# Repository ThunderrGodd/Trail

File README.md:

A copy of Promenade keyboard PCB, based on ChillKB's ice60v2.
<br />It's still WIP, but I don't want to manage it anymore.
<br />Working NEVER tested

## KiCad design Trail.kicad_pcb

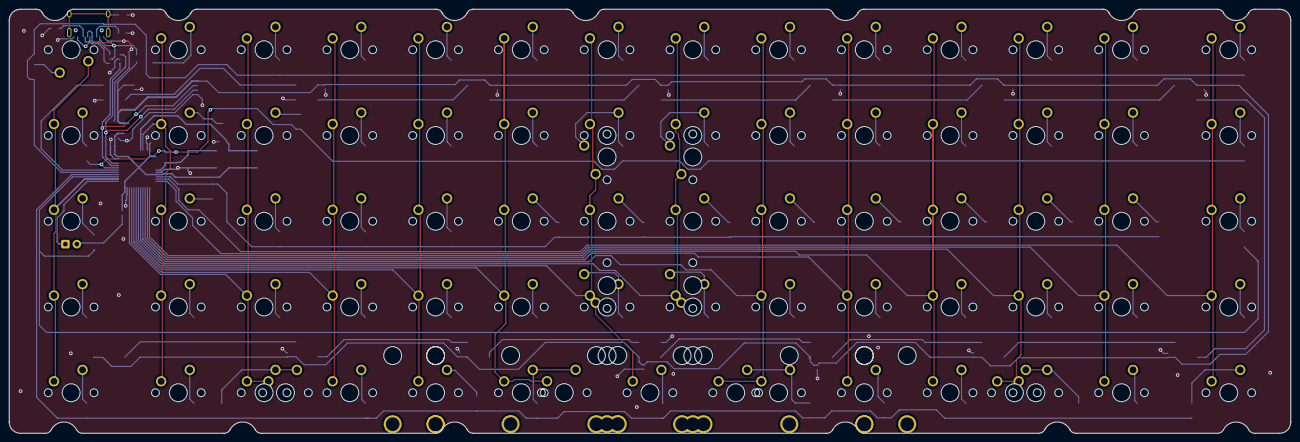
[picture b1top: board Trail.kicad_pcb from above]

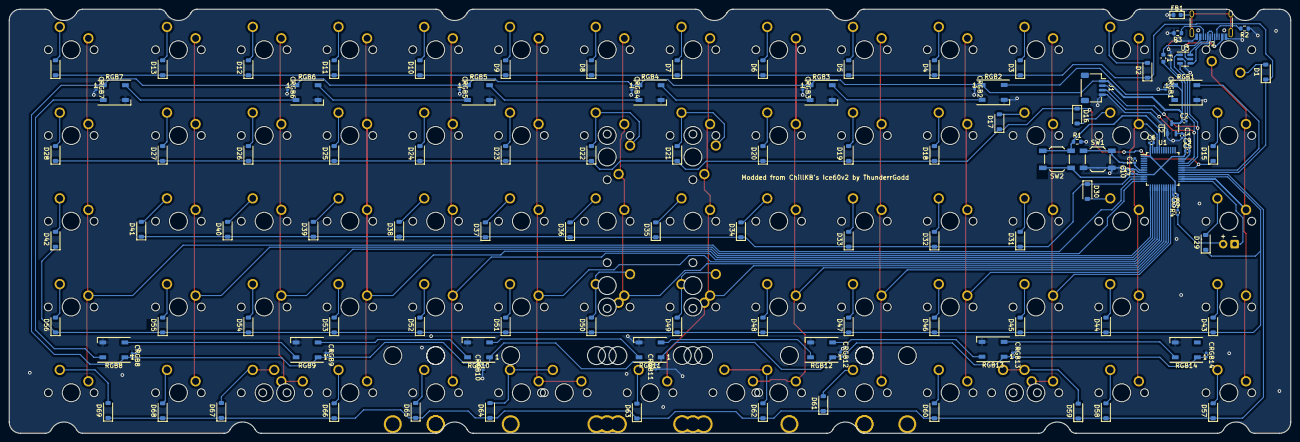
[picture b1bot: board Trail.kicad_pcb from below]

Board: 2 copper layers, 284.7 x 94.2 mm, 205 parts (120 on the bottom side), 117 nets.

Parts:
C1, C5, C6, C7, C8: 100n; C_0402_1005Metric
C2, C3, C10: 1u; C_0402_1005Metric
C4: 4.7u; C_0402_1005Metric
C9: 10n; C_0402_1005Metric
CRGB1, CRGB2, CRGB3, CRGB4, CRGB5, CRGB6, CRGB7, CRGB8, CRGB9, CRGB10, CRGB11, CRGB12, CRGB13, CRGB14: 100n; C_0402_1005Metric
D1, D2, D3, D4, D5, D6, D7, D8, D9, D10, D11, D12, D13, D14, D15, D16, D17, D18, D19, D20, D21, D22, D23, D24, D25, D26, D27, D28, D29, D30, D31, D32, D33, D34, D35, D36, D37, D38, D39, D40, D41, D42, D43, D44, D45, D46, D47, D48, D49, D50, D51, D52, D53, D54, D55, D56, D57, D58, D59, D60, D61, D62, D63, D64, D65, D66, D67, D68, D69: D; D_SOD-123
F1: mSMD110-16V; Fuse_0603_1608Metric
FB1: BLM18KG121TN1D; Ferrite_0603_1608Metric
J1: JST_SH_SM04B-SRSS-TB_1x04; JST_SH_SM04B-SRSS-TB_1x04-1MP_P1.00mm_Horizontal
J2: USB_C_Receptacle_USB2.0_14P; USB_C_Receptacle_HRO_TYPE-C-31-M-12
LED2: LED; LED_MX_3mm-ROT
MX1: ESC; SW_MX_1.5u
MX2: 1; SW_MX_1u
MX3: 2; SW_MX_1u
MX4: 3; SW_MX_1u
MX5: 4; SW_MX_1u
MX6: 5; SW_MX_1u
MX7: 5+; SW_MX_1u
MX8: 6+; SW_MX_1u
MX9: 6; SW_MX_1u
MX10: 7; SW_MX_1u
MX11: 8; SW_MX_1u
MX12: 9; SW_MX_1u
MX13: 0; SW_MX_1u
MX14: MINUS; SW_MX_1.5u
MX15: TAB; SW_MX_1.5u
MX16: Q; SW_MX_1u
MX17: W; SW_MX_1u
MX18: E; SW_MX_1u
MX19: R; SW_MX_1u
MX20: T; SW_MX_1u
MX21: T+; SW_MX_1u
MX22: Y; SW_MX_1u
MX23: I; SW_MX_1u
MX24: O; SW_MX_1u
MX25: P; SW_MX_1u
MX26: L_BRACKET; SW_MX_1u
MX27: R_BRACKET; SW_MX_1u
MX28: BACKSLASH; SW_MX_1.5u
MX29: CAPS; SW_MX_1.5u
MX30: A; SW_MX_1u
MX31: S; SW_MX_1u
MX32: D; SW_MX_1u
MX33: F; SW_MX_1u
MX34: G; SW_MX_1u
MX35: G+; SW_MX_1u
MX36: J; SW_MX_1u
MX37: K; SW_MX_1u
MX38: L; SW_MX_1u
MX39: SEMICOLON; SW_MX_1u
MX40: QUOTE; SW_MX_1u
MX41: ENTER; SW_MX_1u
MX42: R_SPLIT_BACKSPACE; SW_MX_1.5u
MX43: L_SHIFT; SW_MX_1.5u
MX44: Z; SW_MX_1u
MX45: X; SW_MX_1u
MX46: C; SW_MX_1u
MX47: V; SW_MX_1u
MX48: B; SW_MX_1u
MX49: B+; SW_MX_1u
MX50: N; SW_MX_1u
MX51: M; SW_MX_1u
MX52: COMMA; SW_MX_1u
MX53: PERIOD; SW_MX_1u
MX54: FWDSLASH; SW_MX_1u
MX55: R_SHIFT; SW_MX_1u
MX56: R_SPLIT_R_SHIFT; SW_MX_1.5u
MX57: L_CTRL; SW_MX_1.5u
MX58: L_GUI; SW_MX_1u
MX59: L_ALT; SW_MX_1u
MX60, MX61, MX62, MX63, MX64, MX65, MX74, MX75: SPACE; SW_MX_1u
MX66: R_ALT; SW_MX_1u
MX67: R_GUI; SW_MX_1u
MX68: APP; SW_MX_1u
MX69: R_CTRL; SW_MX_1.5u
MX70: T+; SW_MX_1.5u
MX71: Y+; SW_MX_1.5u
MX72: B+; SW_MX_1.5u
MX73: N+; SW_MX_1.5u
MX76: L_ALT_7u; SW_MX_1.5u
MX77: R_ALT_7u; SW_MX_1.5u
R1: 10k; R_0603_1608Metric
R2, R3: 5.1K; R_0603_1608Metric
R4: 470R; R_0402_1005Metric
RGB1, RGB2, RGB3, RGB4, RGB5, RGB6, RGB7, RGB8, RGB9, RGB10, RGB11, RGB12, RGB13, RGB14: WS2812B; LED_WS2812B_PLCC4_5.0x5.0mm_P3.2mm
S1, S2, S3: 2U Stab; STAB_MX_P_2u
S4, S5: 3U stab; STAB_MX_P_3u
S6: 6U Stab; STAB_MX_P_6u
S7: 7U Stab; STAB_MX_P_7u
SW1: RST; SW_SPST_TL3342
SW2: BOOT; SW_SPST_TL3342
U1: STM32F072CBTx; LQFP-48_7x7mm_P0.5mm
U2: XC6206P332MR; SOT-23-3
U3: USBLC6-2SC6; SOT-23-6

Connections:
+3V3: C3.1, C4.1, C5.1, C6.1, C7.1, C8.1, C9.1, C10.1, R4.2, SW2.1, U1.1 (VBAT), U1.9 (VDDA), U1.24 (VDD), U1.36 (VDDIO2), U1.48 (VDD), U2.2 (VO)
+5V: C2.1, CRGB1.1, CRGB2.1, CRGB3.1, CRGB4.1, CRGB5.1, CRGB6.1, CRGB7.1, CRGB8.2, CRGB9.2, CRGB10.2, CRGB11.2, CRGB12.2, CRGB13.2, CRGB14.2, F1.2, J1.1, RGB1.1 (VDD), RGB2.1 (VDD), RGB3.1 (VDD), RGB4.1 (VDD), RGB5.1 (VDD), RGB6.1 (VDD), RGB7.1 (VDD), RGB8.1 (VDD), RGB9.1 (VDD), RGB10.1 (VDD), RGB11.1 (VDD), RGB12.1 (VDD), RGB13.1 (VDD), RGB14.1 (VDD), U2.3 (VI)
BOOT0: R1.1, SW2.2, U1.44 (BOOT0)
CAPSLCK: LED2.1 (K), U1.25 (PB12)
COL00: MX1.1, MX15.1, MX29.1, MX43.1, MX57.1, U1.26 (PB13)
COL01: MX2.1, MX16.1, MX30.1, MX44.1, MX58.1, U1.45 (PB8)
COL02: MX3.1, MX17.1, MX31.1, MX45.1, MX59.1, MX76.1, U1.22 (PB11)
COL03: MX4.1, MX18.1, MX32.1, MX46.1, MX60.1, U1.21 (PB10)
COL04: MX5.1, MX19.1, MX33.1, MX47.1, MX61.1, U1.20 (PB2)
COL05: MX6.1, MX20.1, MX34.1, MX48.1, MX62.1, MX74.1, U1.19 (PB1)
COL06: MX7.1, MX21.1, MX35.1, MX49.1, MX63.1, MX70.1, MX72.1, U1.18 (PB0)
COL07: MX8.1, MX22.1, MX36.1, MX50.1, MX71.1, MX73.1, U1.17 (PA7)
COL08: MX9.1, MX23.1, MX37.1, MX51.1, MX64.1, MX75.1, U1.16 (PA6)
COL09: MX10.1, MX24.1, MX38.1, MX52.1, MX65.1, U1.15 (PA5)
COL10: MX11.1, MX25.1, MX39.1, MX53.1, MX66.1, U1.14 (PA4)
COL11: MX12.1, MX26.1, MX40.1, MX54.1, MX67.1, MX77.1, U1.13 (PA3)
COL12: MX13.1, MX27.1, MX41.1, MX55.1, MX68.1, U1.12 (PA2)
COL13: MX14.1, MX28.1, MX42.1, MX56.1, MX69.1, U1.11 (PA1)
D+: J1.3, U1.33 (PA12), U3.1 (I/O1)
D-: J1.2, U1.32 (PA11), U3.3 (I/O2)
DBUS+: J2.A6 (D+), J2.B6 (D+), U3.6 (I/O1)
DBUS-: J2.A7 (D-), J2.B7 (D-), U3.4 (I/O2)
DIN: RGB1.4 (DIN), U1.30 (PA9)
GND: C1.2, C2.2, C3.2, C4.2, C5.2, C6.2, C7.2, C8.2, C9.2, C10.2, CRGB1.2, CRGB2.2, CRGB3.2, CRGB4.2, CRGB5.2, CRGB6.2, CRGB7.2, CRGB8.1, CRGB9.1, CRGB10.1, CRGB11.1, CRGB12.1, CRGB13.1, CRGB14.1, FB1.1, J1.4, J2.A1 (GND), J2.A12 (GND), J2.B1 (GND), J2.B12 (GND), R1.2, R2.1, R3.2, RGB1.3 (VSS), RGB2.3 (VSS), RGB3.3 (VSS), RGB4.3 (VSS), RGB5.3 (VSS), RGB6.3 (VSS), RGB7.3 (VSS), RGB8.3 (VSS), RGB9.3 (VSS), RGB10.3 (VSS), RGB11.3 (VSS), RGB12.3 (VSS), RGB13.3 (VSS), RGB14.3 (VSS), SW1.2, U1.8 (VSSA), U1.23 (VSS), U1.35 (VSS), U1.47 (VSS), U2.1 (GND), U3.2 (GND)
GNDPWR: FB1.2, J2.S1 (SHIELD)
unnamed: D1.2 (A), MX1.2
unnamed: D2.2 (A), MX2.2
unnamed: D3.2 (A), MX3.2
unnamed: D4.2 (A), MX4.2
unnamed: D5.2 (A), MX5.2
unnamed: D6.2 (A), MX6.2
unnamed: D7.2 (A), MX7.2
unnamed: D8.2 (A), MX8.2
unnamed: D9.2 (A), MX9.2
unnamed: D10.2 (A), MX10.2
unnamed: D11.2 (A), MX11.2
unnamed: D12.2 (A), MX12.2
unnamed: D13.2 (A), MX13.2
unnamed: D14.2 (A), MX14.2
unnamed: D15.2 (A), MX15.2
unnamed: D16.2 (A), MX16.2
unnamed: D17.2 (A), MX17.2
unnamed: D18.2 (A), MX18.2
unnamed: D19.2 (A), MX19.2
unnamed: D20.2 (A), MX20.2
unnamed: D21.2 (A), MX21.2, MX70.2
unnamed: D22.2 (A), MX22.2, MX71.2
unnamed: D23.2 (A), MX23.2
unnamed: D24.2 (A), MX24.2
unnamed: D25.2 (A), MX25.2
unnamed: D26.2 (A), MX26.2
unnamed: D27.2 (A), MX27.2
unnamed: D28.2 (A), MX28.2
unnamed: D29.2 (A), MX29.2
unnamed: D30.2 (A), MX30.2
unnamed: D31.2 (A), MX31.2
unnamed: D32.2 (A), MX32.2
unnamed: D33.2 (A), MX33.2
unnamed: D34.2 (A), MX34.2
unnamed: D35.2 (A), MX35.2
unnamed: D36.2 (A), MX36.2
unnamed: D37.2 (A), MX37.2
unnamed: D38.2 (A), MX38.2
unnamed: D39.2 (A), MX39.2
unnamed: D40.2 (A), MX40.2
unnamed: D41.2 (A), MX41.2
unnamed: D42.2 (A), MX42.2
unnamed: D43.2 (A), MX43.2
unnamed: D44.2 (A), MX44.2
unnamed: D45.2 (A), MX45.2
unnamed: D46.2 (A), MX46.2
unnamed: D47.2 (A), MX47.2
unnamed: D48.2 (A), MX48.2
unnamed: D49.2 (A), MX49.2, MX72.2
unnamed: D50.2 (A), MX50.2, MX73.2
unnamed: D51.2 (A), MX51.2
unnamed: D52.2 (A), MX52.2
unnamed: D53.2 (A), MX53.2
unnamed: D54.2 (A), MX54.2
unnamed: D55.2 (A), MX55.2
unnamed: D56.2 (A), MX56.2
unnamed: D57.2 (A), MX57.2
unnamed: D58.2 (A), MX58.2
unnamed: D59.2 (A), MX59.2, MX76.2
unnamed: D60.2 (A), MX60.2
unnamed: D61.2 (A), MX61.2
unnamed: D62.2 (A), MX62.2, MX74.2
unnamed: D63.2 (A), MX63.2
unnamed: D64.2 (A), MX64.2, MX75.2
unnamed: D65.2 (A), MX65.2
unnamed: D66.2 (A), MX66.2
unnamed: D67.2 (A), MX67.2, MX77.2
unnamed: D68.2 (A), MX68.2
unnamed: D69.2 (A), MX69.2
unnamed: J2.A5 (CC1), R2.2
unnamed: J2.B5 (CC2), R3.1
unnamed: LED2.2 (A), R4.1
unnamed: RGB1.2 (DOUT), RGB2.4 (DIN)
unnamed: RGB2.2 (DOUT), RGB3.4 (DIN)
unnamed: RGB3.2 (DOUT), RGB4.4 (DIN)
unnamed: RGB4.2 (DOUT), RGB5.4 (DIN)
unnamed: RGB5.2 (DOUT), RGB6.4 (DIN)
unnamed: RGB6.2 (DOUT), RGB7.4 (DIN)
unnamed: RGB7.2 (DOUT), RGB8.4 (DIN)
unnamed: RGB8.2 (DOUT), RGB9.4 (DIN)
unnamed: RGB9.2 (DOUT), RGB10.4 (DIN)
unnamed: RGB10.2 (DOUT), RGB11.4 (DIN)
unnamed: RGB11.2 (DOUT), RGB12.4 (DIN)
unnamed: RGB12.2 (DOUT), RGB13.4 (DIN)
unnamed: RGB13.2 (DOUT), RGB14.4 (DIN)
ROW0: D1.1 (K), D2.1 (K), D3.1 (K), D4.1 (K), D5.1 (K), D6.1 (K), D7.1 (K), D8.1 (K), D9.1 (K), D10.1 (K), D11.1 (K), D12.1 (K), D13.1 (K), D14.1 (K), U1.29 (PA8)
ROW1: D15.1 (K), D16.1 (K), D17.1 (K), D18.1 (K), D19.1 (K), D20.1 (K), D21.1 (K), D22.1 (K), D23.1 (K), D24.1 (K), D25.1 (K), D26.1 (K), D27.1 (K), D28.1 (K), U1.31 (PA10)
ROW2: D30.1 (K), D31.1 (K), D32.1 (K), D33.1 (K), D34.1 (K), D35.1 (K), D36.1 (K), D37.1 (K), D38.1 (K), D39.1 (K), D40.1 (K), D41.1 (K), U1.10 (PA0)
ROW3: D29.1 (K), D42.1 (K), D43.1 (K), D44.1 (K), D45.1 (K), D46.1 (K), D47.1 (K), D48.1 (K), D49.1 (K), D50.1 (K), D51.1 (K), D52.1 (K), D53.1 (K), D54.1 (K), D55.1 (K), D56.1 (K), U1.27 (PB14)
ROW4: D57.1 (K), D58.1 (K), D59.1 (K), D60.1 (K), D61.1 (K), D62.1 (K), D63.1 (K), D64.1 (K), D65.1 (K), D66.1 (K), D67.1 (K), D68.1 (K), D69.1 (K), U1.28 (PB15)
VBUS: F1.1, J2.A4 (VBUS), J2.A9 (VBUS), J2.B4 (VBUS), J2.B9 (VBUS), U3.5 (VBUS)
~RST: C1.1, SW1.1, U1.7 (NRST)

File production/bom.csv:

Designator,Footprint,Quantity,Value,LCSC Part #
"C1, C5, C6, C7, C8, CRGB1, CRGB10, CRGB11, CRGB12, CRGB13, CRGB14, CRGB2, CRGB3, CRGB4, CRGB5, CRGB6, CRGB7, CRGB8, CRGB9",402,19,100n,
"C10, C2, C3",402,3,1u,
C4,402,1,4.7u,
C9,402,1,10n,
"D1, D10, D11, D12, D13, D14, D15, D16, D17, D18, D19, D2, D20, D21, D22, D23, D24, D25, D26, D27, D28, D29, D3, D30, D31, D32, D33, D34, D35, D36, D37, D38, D39, D4, D40, D41, D42, D43, D44, D45, D46, D47, D48, D49, D5, D50, D51, D52, D53, D54, D55, D56, D57, D58, D59, D6, D60, D61, D62, D63, D64, D65, D66, D67, D68, D69, D7, D8, D9",D_SOD-123,69,1N4148,
F1,603,1,mSMD110-16V,
FB1,Ferrite_0603_1608Metric,1,BLM18KG121TN1D,
R1,603,1,10k,
"R2, R3",603,2,5.1K,
R4,402,1,470R,C25117
"RGB1, RGB10, RGB11, RGB12, RGB13, RGB14, RGB2, RGB3, RGB4, RGB5, RGB6, RGB7, RGB8, RGB9",LED_WS2812B_PLCC4_5.0x5.0mm_P3.2mm,14,WS2812B,
SW1,SW_SPST_TL3342,1,RST,
SW2,SW_SPST_TL3342,1,BOOT,
U1,LQFP-48_7x7mm_P0.5mm,1,STM32F072CBTx,
U2,SOT-23-3,1,XC6206P332MR,
U3,SOT-23-6,1,USBLC6-2SC6,

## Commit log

2024-05-09 CERN licence
2024-05-09 add library
2024-05-09 library update
2024-05-09 add qmk source
